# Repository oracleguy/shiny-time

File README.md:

# Shiny Time
Digital clock and multi-mode countdown timer. Displays the current time or different countdown timers with web configuration.

# Buttons

There are two configurable buttons that when pressed will show the countdown in days to a specific date. There are two day countdown modes:
- Specific Day: A day that repeats once per year. ex. Birthday
- Specific Date: A specific day and year. ex: some special event

The modes and the dates are configurable in the web interface.

The day countdown timer should always show the whole day remaining. For example if the countdown was to December 25th, any time on December 24th, it would read "1".

# Time Countdown Timers

The time countdown timers are used to run shorter countdown timers. When a countdown timer is running, the device displays the time remaining instead of the current time. The countdown timers can be started via the web interface.

# Web Interface

The web interface displays what the device is currently displaying. This interface lets set certain options and start and stop timers.

# Hardware

The device is based on a Raspberry Pi Zero 2W.

## GPIO Expander

The buttons and their integrated lights will be connected to a GPIO epander. This expander is connected via the I2C bus and wires two interrupt pins to the Pi.

## Seven Segment Display

The seven segment display will be used to display the current time or the countdown timers. This display will be connected via the I2C bus.

## Web application architecture

The web interface will be generated as a mostly static site with Zola. It will
not initially use a full single-page application framework such as React or
Angular. A small amount of JavaScript can call the Python API and update the
dashboard, while keeping the interface lightweight for the Raspberry Pi Zero
2W.

The Python application uses Flask 3.1.3 and exposes the WSGI application
through the application factory `create_app`. The production server is
Waitress 3.0.2. The development server can be started with `make server`; the
production WSGI server can be started with `make production-server`.

The application factory accepts an optional device implementation:

```python
app = create_app(device_instance=fake_device)
```

This keeps hardware construction out of module import time and allows the web
application to be tested without Raspberry Pi hardware. In production,
`create_app()` constructs the real device when the application starts.

The API is organized around device state and user actions rather than direct
GPIO operations. Physical buttons and web requests should eventually use the
same application services and timer state machine. The initial endpoints are:

```text
GET /api/health   Basic service health check
GET /api/status   Current device status
```

Timer, configuration, and Wi-Fi setup endpoints will be added behind this
boundary. The frontend and API are intended to be served from the same origin,
so cross-origin configuration should not be necessary.

## HTTP and network security

The device will serve HTTP locally rather than requiring HTTPS certificates on
the Raspberry Pi. This applies to both the normal home-LAN interface and the
setup portal at `http://192.168.4.1`. The setup hotspot is isolated and the
setup authorization code is a physical-presence check, not high-security
authentication.

The device must not be exposed directly to the public Internet or through
router port forwarding. Users who need remote access or who are on an
untrusted network should provide the security boundary outside the device,
using a VPN or a reverse proxy that terminates HTTPS. The application should
never log Wi-Fi passwords.

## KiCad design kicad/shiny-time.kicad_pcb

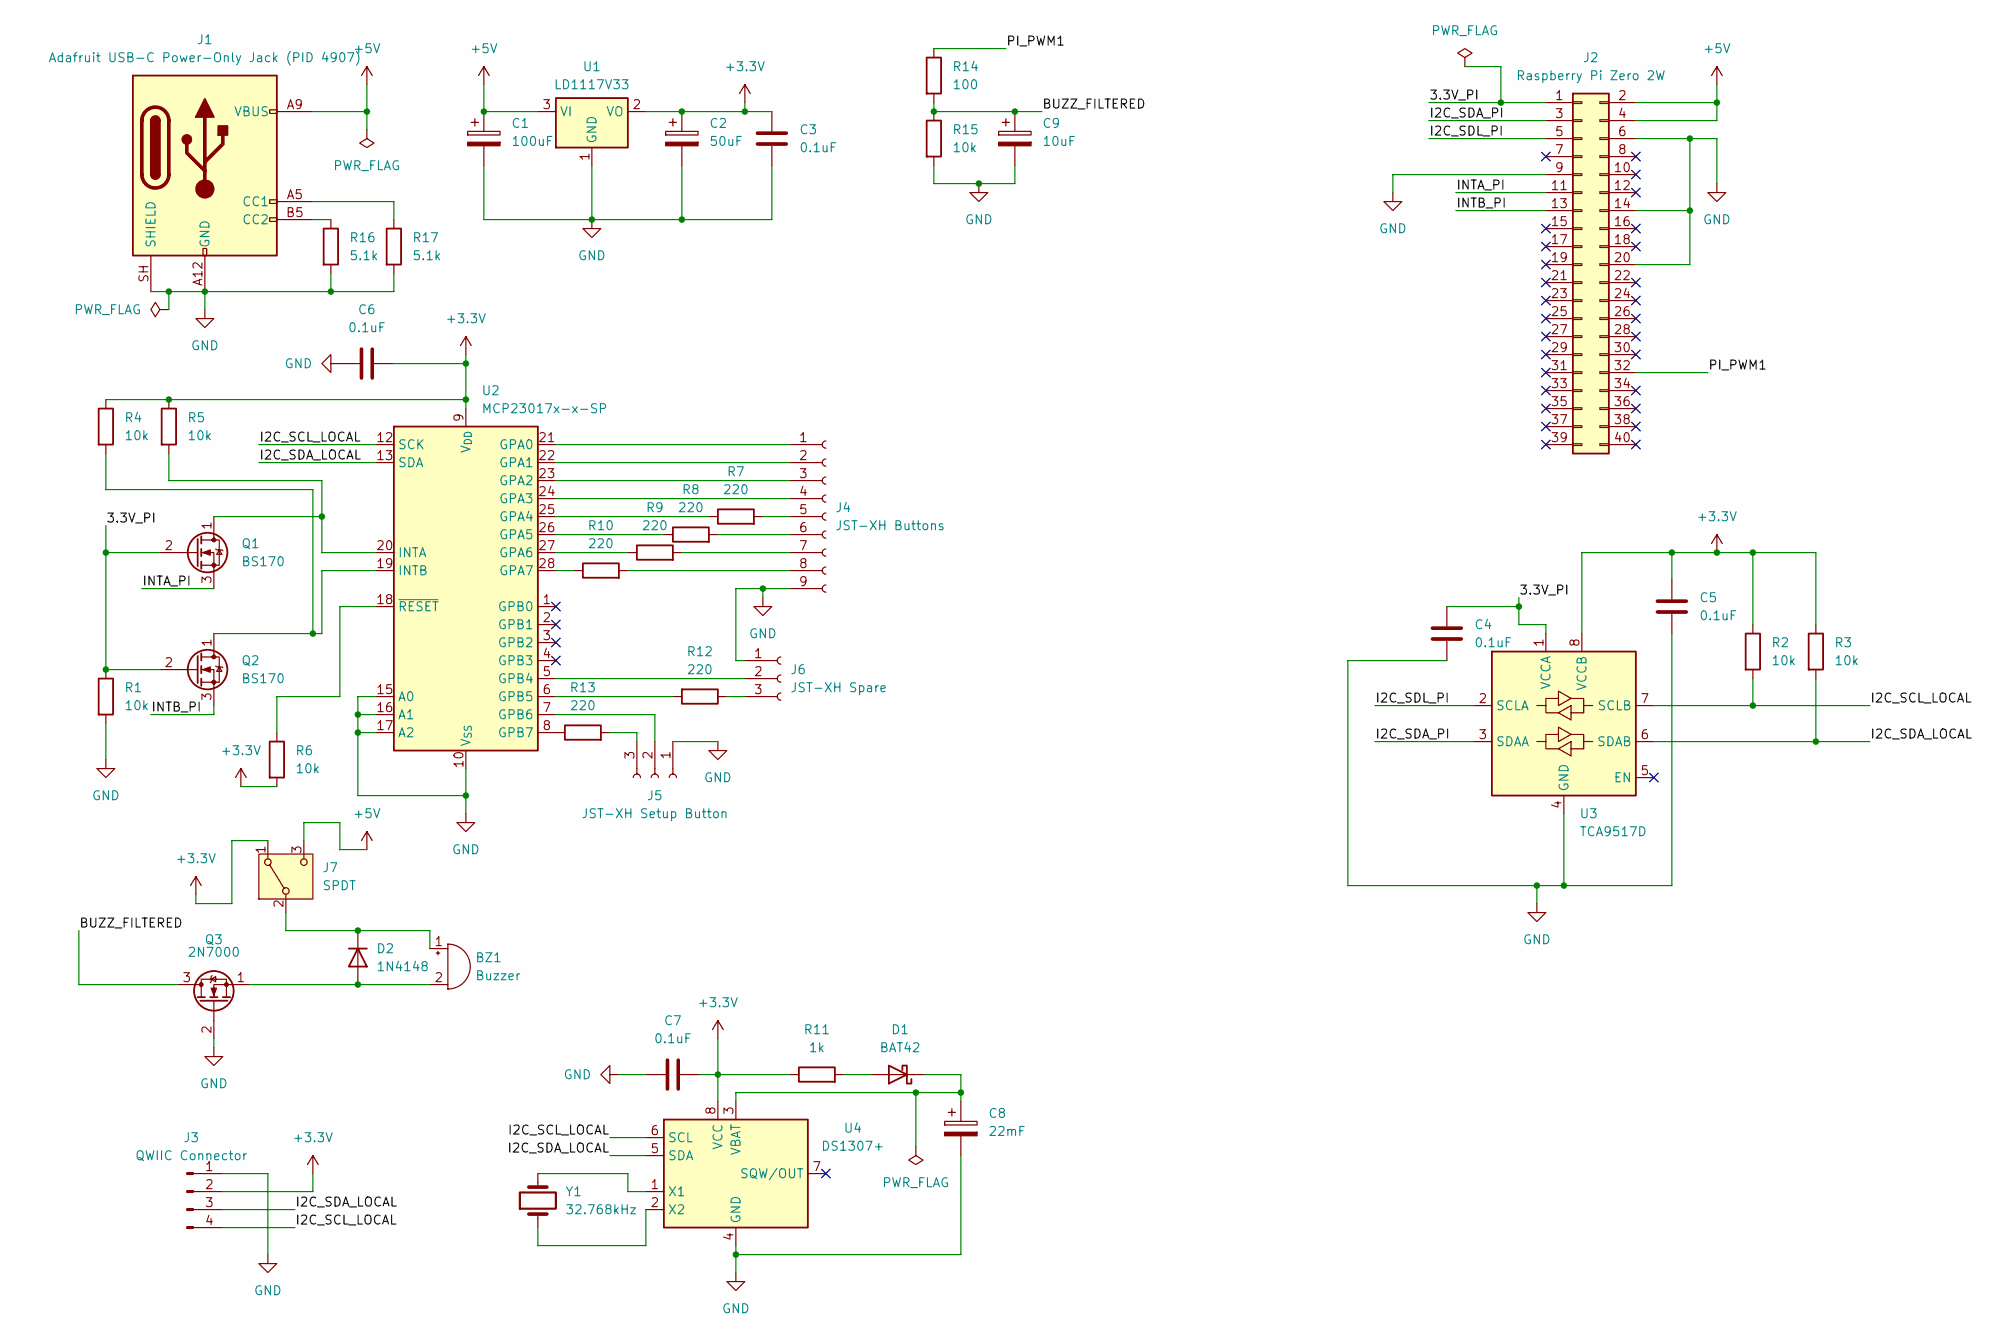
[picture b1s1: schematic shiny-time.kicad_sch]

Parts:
BZ1: Buzzer; Buzzer_12x9.5RM7.6
C1: 100uF; CP_Radial_D5.0mm_P2.00mm; Digikey_PN 1189-1224-ND
C2: 50uF; CP_Radial_D5.0mm_P2.00mm; Digikey_PN 1189-1148-ND
C3, C4, C5, C6, C7: 0.1uF; C_Disc_D5.0mm_W2.5mm_P2.50mm; Digikey_PN 399-4264-ND
C8: 22mF; CP_Radial_D12.5mm_P5.00mm; Digikey_PN 399-18542-ND
C9: 10uF; C_Disc_D5.0mm_W2.5mm_P5.00mm; Digikey_PN 399-13968-ND
D1: BAT42; D_DO-35_SOD27_P10.16mm_Horizontal; Digikey_PN 497-2495-1-ND
D2: 1N4148; D_DO-35_SOD27_P7.62mm_Horizontal; Digikey_PN 1N4148FS-ND
J1: Adafruit USB-C Power-Only Jack (PID 4907); USB_C_Receptacle_GCT_USB4125-xx-x_6P_TopMnt_Horizontal
J2: Raspberry Pi Zero 2W; Raspberry_Pi_Zero_Socketed_THT_FaceDown_MountingHoles; Digikey_PN 2223-SSK04-FPH-254-B20-ND
J3: QWIIC Connector; JST_SH_BM04B-SRSS-TB_1x04-1MP_P1.00mm_Vertical
J4: JST-XH Buttons; JST_XH_B9B-XH-A_1x09_P2.50mm_Vertical
J5: JST-XH Setup Button; JST_XH_B3B-XH-A_1x03_P2.50mm_Vertical
J6: JST-XH Spare; JST_XH_B3B-XH-A_1x03_P2.50mm_Vertical
J7: SPDT; SW_E-Switch_EG1271_SPDT; Digikey_PN EG1918-ND
Q1, Q2: BS170; TO-92_Inline; Digikey_PN BS170-ND
Q3: 2N7000; TO-92_Inline; Digikey_PN 2N7000FS-ND
R1, R2, R3, R4, R5, R6, R15: 10k; R_Axial_DIN0204_L3.6mm_D1.6mm_P5.08mm_Horizontal; Digikey_PN CF18JT10K0CT-ND
R7, R8, R9, R10, R12, R13: 220; R_Axial_DIN0204_L3.6mm_D1.6mm_P5.08mm_Horizontal; Digikey_PN CF18JT220RCT-ND
R11: 1k; R_Axial_DIN0204_L3.6mm_D1.6mm_P5.08mm_Horizontal; Digikey_PN CF18JT1K00CT-ND
R14: 100; R_Axial_DIN0204_L3.6mm_D1.6mm_P5.08mm_Horizontal; Digikey_PN CF18JT100RCT-ND
R16, R17: 5.1k; R_Axial_DIN0204_L3.6mm_D1.6mm_P5.08mm_Horizontal; Digikey_PN S5.1KCACT-ND
U1: LD1117V33; TO-220-3_Vertical; Digikey_PN 497-1491-5-ND
U2: MCP23017x-x-SP; DIP-28_W7.62mm; Digikey_PN MCP23017-E/SP-ND
U3: TCA9517D; SOIC-8_3.9x4.9mm_P1.27mm; Digikey_PN 296-39221-1-ND
U4: DS1307+; DIP-8_W7.62mm; Digikey_PN DS1307+-ND
Y1: 32.768kHz; Crystal_Round_D2.0mm_Vertical; Digikey_PN 535-9032-ND

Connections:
+3.3V: C2.1, C3.1, C5.1, C6.2, C7.2, J3.2, J7.1 (A), R2.1, R3.1, R4.1, R5.1, R6.2, R11.1, U1.2 (VO), U2.9 (V_{DD}), U3.8 (VCCB), U4.8 (VCC)
+5V: C1.1, J1.A9 (VBUS), J1.B9 (VBUS), J2.2, J2.4, J7.3 (C), U1.3 (VI)
/3.3V_PI: C4.1, J2.1, Q1.2 (G), Q2.2 (G), R1.1, U3.1 (VCCA)
/BUZZ_FILTERED: C9.1, Q3.3 (D), R14.2, R15.1
/I2C_SCL_LOCAL: J3.4, R2.2, U2.12 (SCK), U3.7 (SCLB), U4.6 (SCL)
/I2C_SDA_LOCAL: J3.3, R3.2, U2.13 (SDA), U3.6 (SDAB), U4.5 (SDA)
/I2C_SDA_PI: J2.3, U3.3 (SDAA)
/I2C_SDL_PI: J2.5, U3.2 (SCLA)
/INTA_PI: J2.11, Q1.3 (S)
/INTB_PI: J2.13, Q2.3 (S)
/PI_PWM1: J2.32, R14.1
GND: C1.2, C2.2, C3.2, C4.2, C5.2, C6.1, C7.1, C8.2, C9.2, J1.A12 (GND), J1.B12 (GND), J1.SH (SHIELD), J2.6, J2.9, J2.14, J2.20, J3.1, J4.9, J5.1, J6.1, Q3.2 (G), R1.2, R15.2, R16.2, R17.2, U1.1 (GND), U2.10 (V_{SS}), U2.15 (A0), U2.16 (A1), U2.17 (A2), U3.4 (GND), U4.4 (GND)
unnamed: BZ1.1 (+), D2.1 (K), J7.2 (B)
unnamed: BZ1.2 (-), D2.2 (A), Q3.1 (S)
unnamed: D1.2 (A), R11.2
unnamed: C8.1, D1.1 (K), U4.3 (VBAT)
unnamed: J1.A5 (CC1), R17.1
unnamed: J1.B5 (CC2), R16.1
unnamed: J4.1, U2.21 (GPA0)
unnamed: J4.2, U2.22 (GPA1)
unnamed: J4.3, U2.23 (GPA2)
unnamed: J4.4, U2.24 (GPA3)
unnamed: J4.5, R7.2
unnamed: J4.6, R8.2
unnamed: J4.7, R9.2
unnamed: J4.8, R10.2
unnamed: J5.2, U2.7 (GPB6)
unnamed: J5.3, R13.2
unnamed: J6.2, U2.5 (GPB4)
unnamed: J6.3, R12.1
unnamed: Q1.1 (D), R5.2, U2.20 (INTA)
unnamed: Q2.1 (D), R4.2, U2.19 (INTB)
unnamed: R7.1, U2.25 (GPA4)
unnamed: R8.1, U2.26 (GPA5)
unnamed: R9.1, U2.27 (GPA6)
unnamed: R10.1, U2.28 (GPA7)
unnamed: R12.2, U2.6 (GPB5)
unnamed: R13.1, U2.8 (GPB7)
unnamed: R6.1, U2.18 (~RESET)
unnamed: U4.1 (X1), Y1.2
unnamed: U4.2 (X2), Y1.1

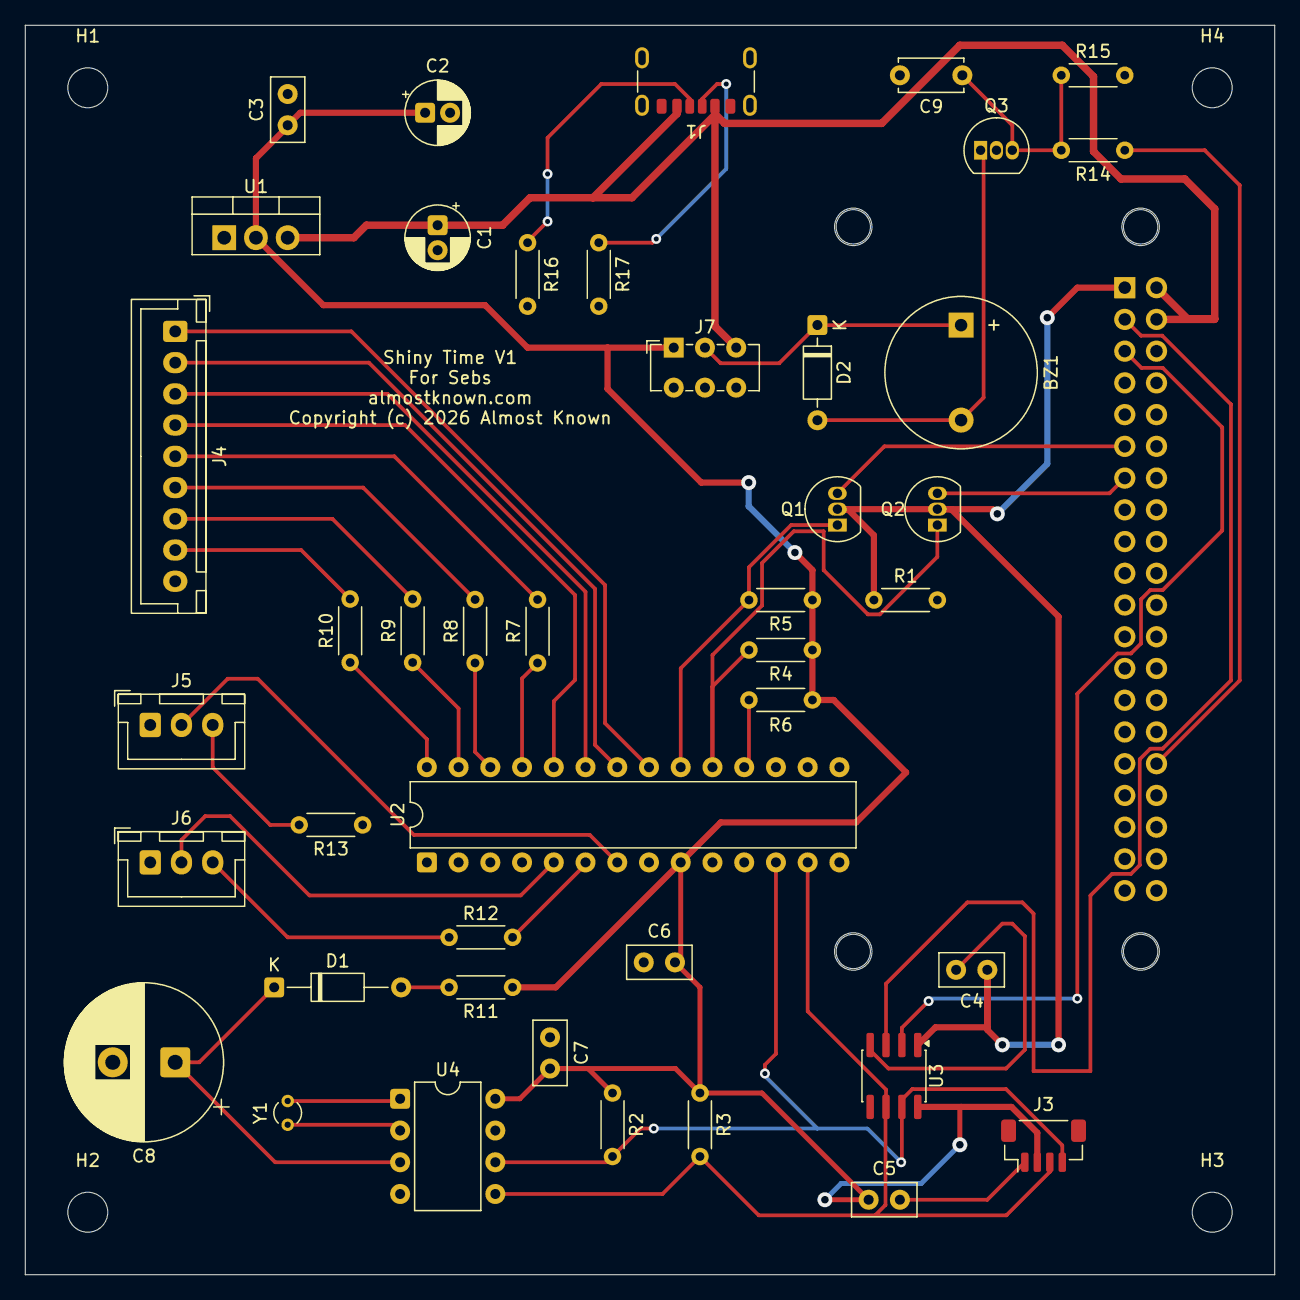
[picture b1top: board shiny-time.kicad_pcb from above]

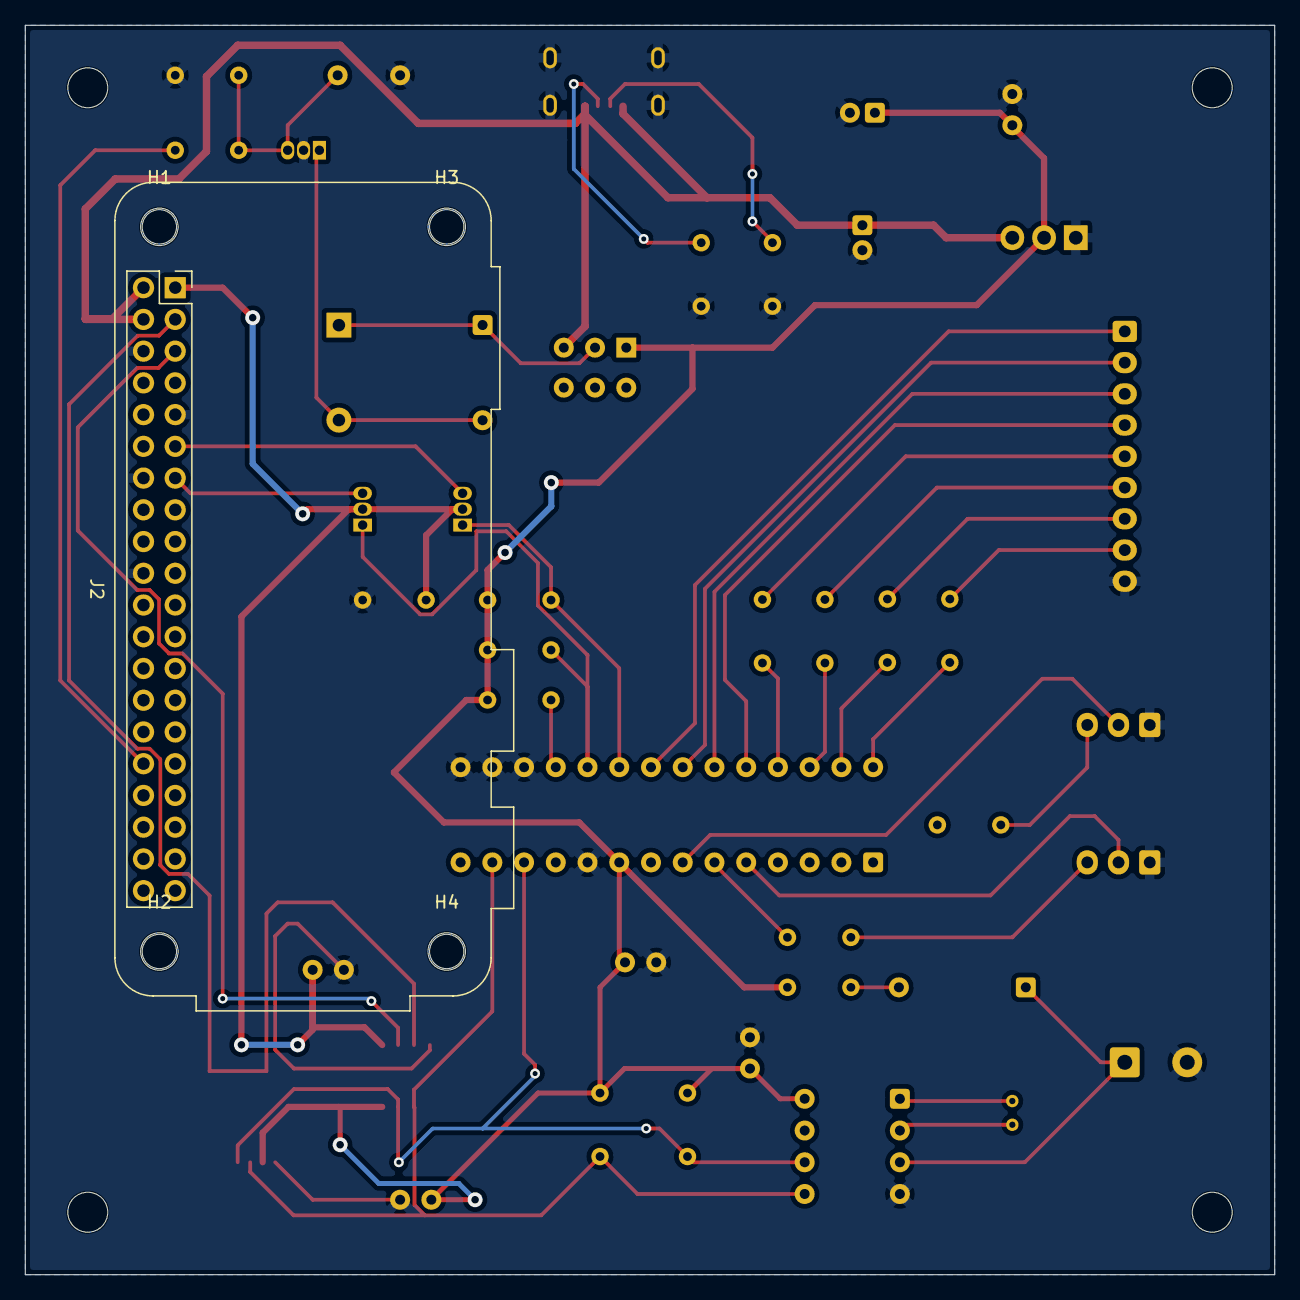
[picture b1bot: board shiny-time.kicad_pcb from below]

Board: 2 copper layers, 100.0 x 100.0 mm, 52 parts (5 on the bottom side), 41 nets.

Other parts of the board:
H1, H2, H3, H4: MountingHole_3.2mm_M3
H1#2, H2#2, H3#2, H4#2: MountingHole_3mm

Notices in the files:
kicad/shiny-time.kicad_pcb:
Copyright (c) 2026 Almost Known
